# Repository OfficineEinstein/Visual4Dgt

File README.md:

# Visual4Dgt 
---
Scheda di visualizzazione con 4 digit in multiplexing
usa un DM9368 e 4 display sette segmenti tipo FND500
controllo digit mediante 2N3904 o 2N2222
previsto per prove con schede arduino/maker uno o compatibili

---
Make with Kicad 5.1.10; CC-BY-SA 3
---

Display board with 4 digits in multiplexing
uses a DM9368 and 4 seven-segment displays type FND500
digit control by 2N3904 or 2N222
intended for testing with arduino/maker one or compatible boards

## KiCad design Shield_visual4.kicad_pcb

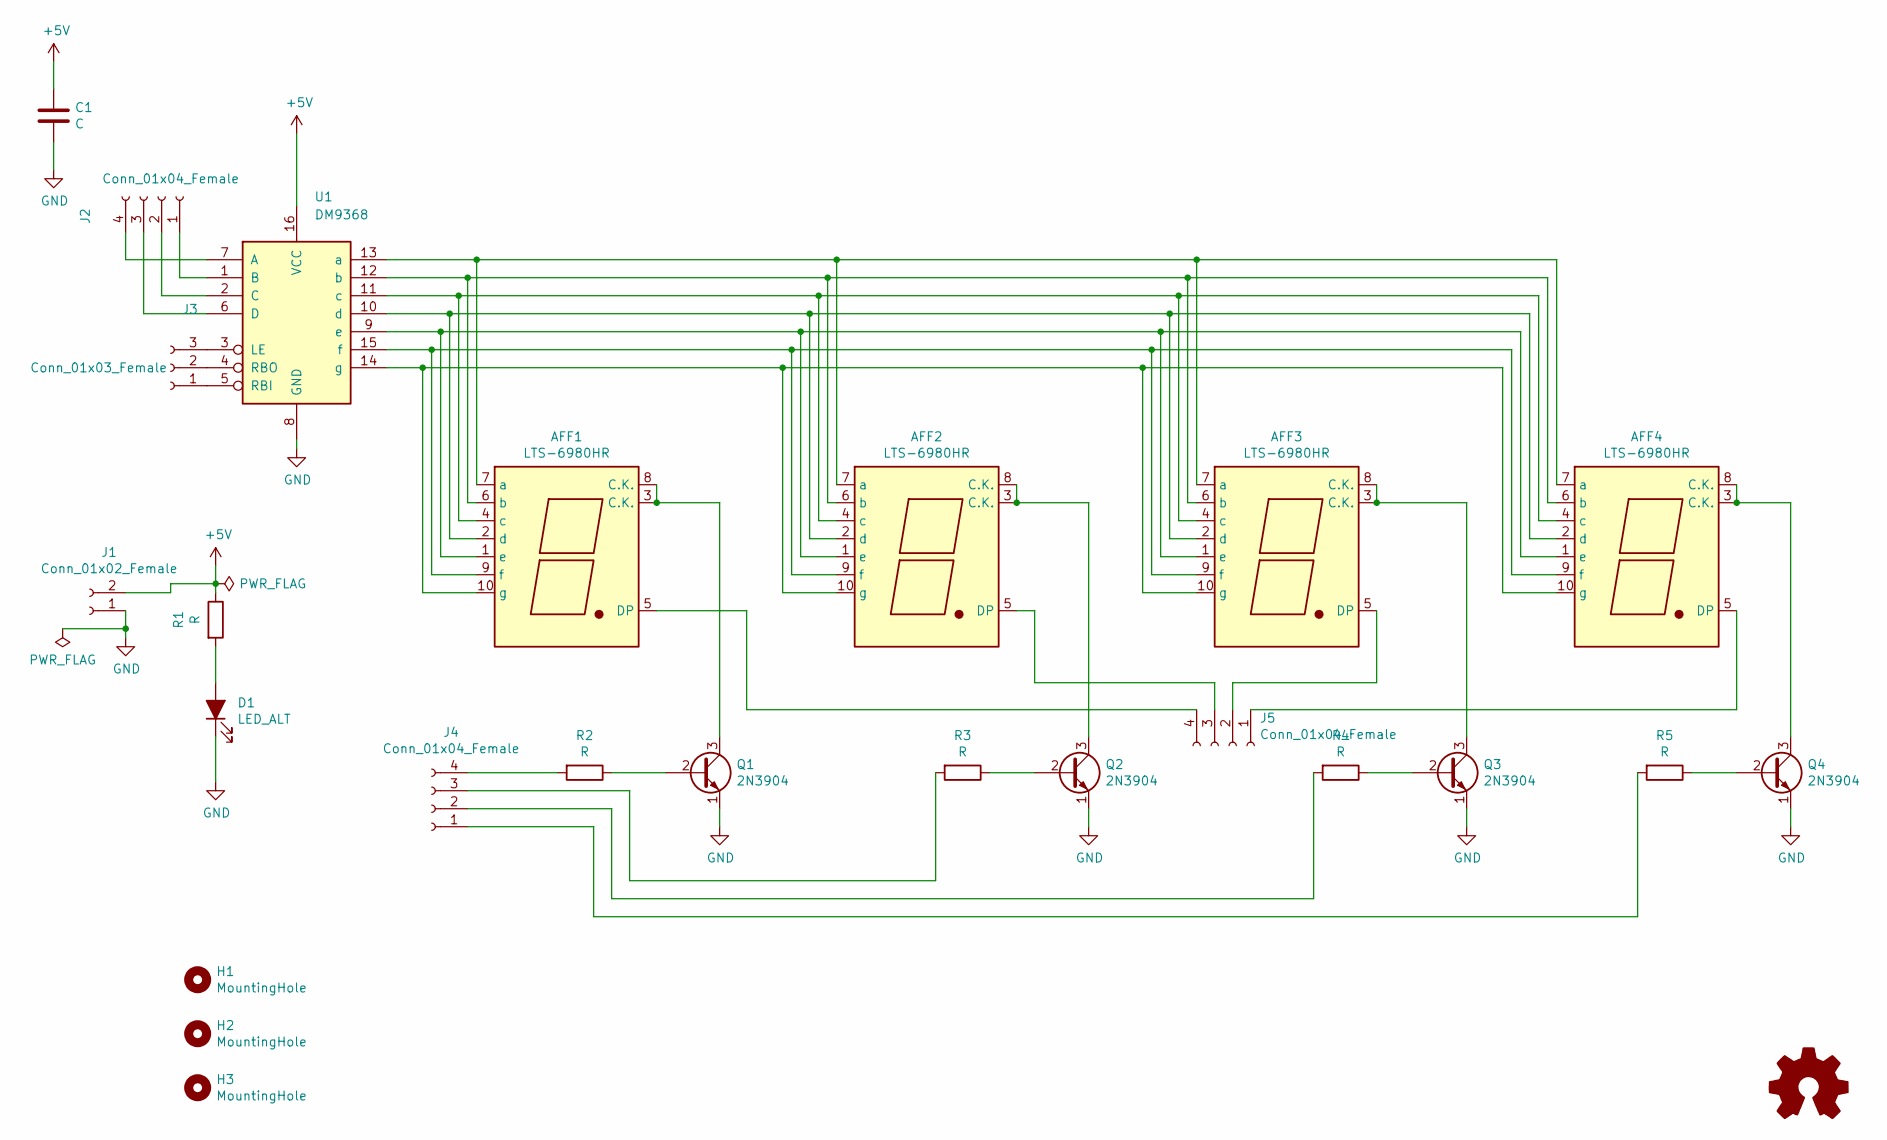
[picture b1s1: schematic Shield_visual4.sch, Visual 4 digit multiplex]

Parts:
AFF1, AFF2, AFF3, AFF4: LTS-6980HR; 7SegmentLED_LTS6760_LTS6780
C1: C; C_Disc_D7.5mm_W2.5mm_P5.00mm
D1: LED_ALT; LED_D5.0mm
H1, H2, H3: MountingHole; MountingHole_3.2mm_M3
J1: Conn_01x02_Female; PinSocket_1x02_P2.54mm_Vertical
J2, J4, J5: Conn_01x04_Female; PinSocket_1x04_P2.54mm_Vertical
J3: Conn_01x03_Female; PinSocket_1x03_P2.54mm_Vertical
Q1, Q2, Q3, Q4: 2N3904; TO-92_Inline
R1, R2, R3, R4, R5: R; R_Axial_DIN0207_L6.3mm_D2.5mm_P10.16mm_Horizontal
U1: DM9368; DIP-16_W7.62mm_LongPads

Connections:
+5V: C1.1, J1.2, R1.1, U1.16 (VCC)
GND: C1.2, D1.1 (K), J1.1, Q1.1 (E), Q2.1 (E), Q3.1 (E), Q4.1 (E), U1.8 (GND)
unnamed: AFF1.1 (e), AFF2.1 (e), AFF3.1 (e), AFF4.1 (e), U1.9 (e)
unnamed: AFF1.2 (d), AFF2.2 (d), AFF3.2 (d), AFF4.2 (d), U1.10 (d)
unnamed: AFF1.3 (C.K.), AFF1.8 (C.K.), Q1.3 (C)
unnamed: AFF1.4 (c), AFF2.4 (c), AFF3.4 (c), AFF4.4 (c), U1.11 (c)
unnamed: AFF1.5 (DP), J5.4
unnamed: AFF1.6 (b), AFF2.6 (b), AFF3.6 (b), AFF4.6 (b), U1.12 (b)
unnamed: AFF1.7 (a), AFF2.7 (a), AFF3.7 (a), AFF4.7 (a), U1.13 (a)
unnamed: AFF1.9 (f), AFF2.9 (f), AFF3.9 (f), AFF4.9 (f), U1.15 (f)
unnamed: AFF1.10 (g), AFF2.10 (g), AFF3.10 (g), AFF4.10 (g), U1.14 (g)
unnamed: AFF2.3 (C.K.), AFF2.8 (C.K.), Q2.3 (C)
unnamed: AFF2.5 (DP), J5.3
unnamed: AFF3.3 (C.K.), AFF3.8 (C.K.), Q3.3 (C)
unnamed: AFF3.5 (DP), J5.2
unnamed: AFF4.3 (C.K.), AFF4.8 (C.K.), Q4.3 (C)
unnamed: AFF4.5 (DP), J5.1
unnamed: D1.2 (A), R1.2
unnamed: J2.1, U1.1 (B)
unnamed: J2.2, U1.2 (C)
unnamed: J2.3, U1.6 (D)
unnamed: J2.4, U1.7 (A)
unnamed: J3.1, U1.5 (RBI)
unnamed: J3.2, U1.4 (RBO)
unnamed: J3.3, U1.3 (LE)
unnamed: J4.1, R5.2
unnamed: J4.2, R4.2
unnamed: J4.3, R3.2
unnamed: J4.4, R2.2
unnamed: Q1.2 (B), R2.1
unnamed: Q2.2 (B), R3.1
unnamed: Q3.2 (B), R4.1
unnamed: Q4.2 (B), R5.1

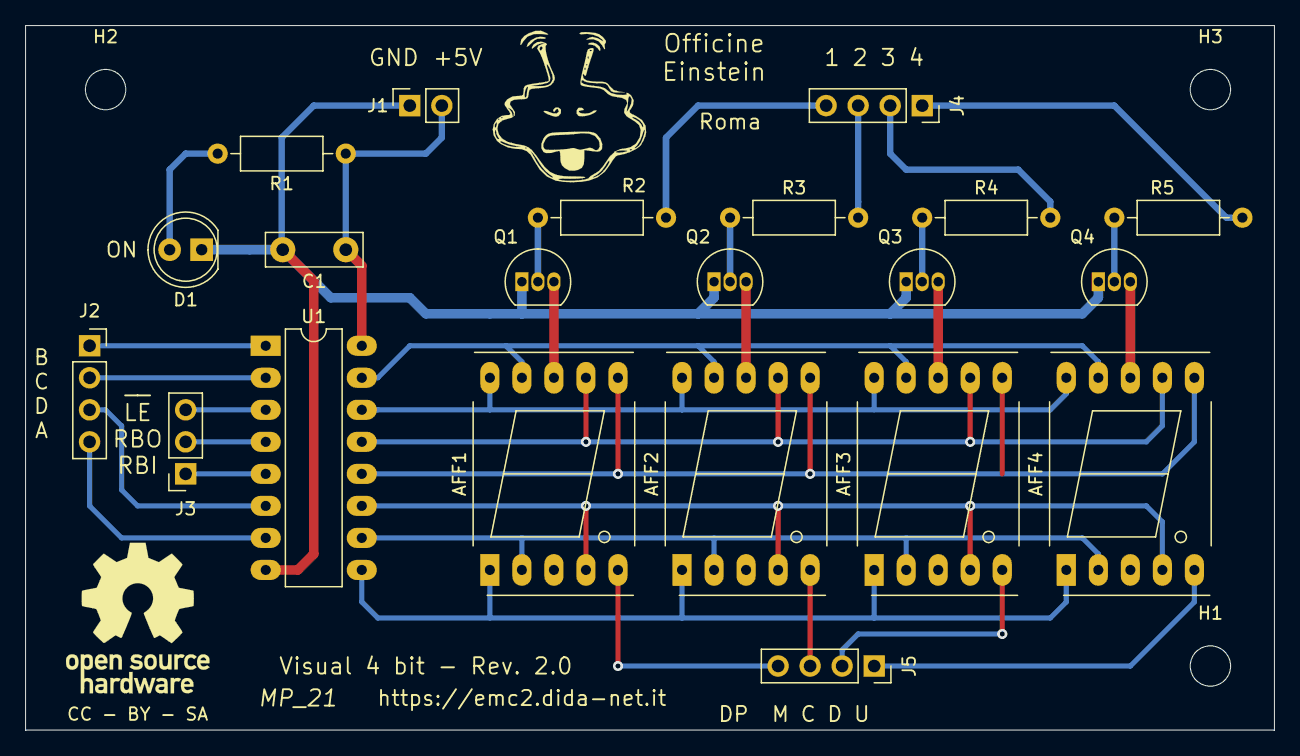
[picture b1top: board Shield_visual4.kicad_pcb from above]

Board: 2 copper layers, 99.1 x 55.9 mm, 24 parts (0 on the bottom side), 33 nets.
